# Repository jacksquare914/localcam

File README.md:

# LocalCam-1 — a local-only WiFi camera

A small 4-layer board that turns a **Luckfox Core1106** system-on-module (Rockchip
RV1106G3) into a network camera that never talks to anyone's cloud. A MIPI CSI-2 sensor
comes in over an FPC, the module encodes H.264/H.265 on-chip, and the stream is served
over RTSP to a local [Frigate](https://frigate.video/) NVR. Object detection runs on the
module's own 1 TOPS NPU, on the camera, not on a server and not on someone else's GPU.

**75 × 44 mm, 4 layers, 1.6 mm, built by JLCPCB.** USB-C in, microSD for storage, a
debug UART header and a recovery button.

> **Status: not ready to order.** 226 of 228 netted pads are connected. Two signals still
> need a trace and both need a part nudged rather than more routing effort — see
> [What is still open](#what-is-still-open). Everything else has been verified; the
> evidence is in [`logs/`](logs/).

---

## Why this board exists

Every consumer camera in this class wants an account, an app, and an outbound
connection. The goal here is the opposite: a camera that is useful precisely because it
is isolated. Four requirements drove the whole design.

1. **Nothing leaves the LAN.** No cloud service, no phone-home, no vendor account. RTSP
   to a local NVR and that is all.
2. **Detection happens on the camera.** The RV1106G3's NPU runs the model, so there is
   no video streaming off-box just so a server can look at it.
3. **It must be repairable and legible.** A board you cannot read is a board you cannot
   fix. That drove the routing style (below) as much as any electrical requirement.
4. **One cable.** USB-C supplies it; everything else is optional.

## What is on it

| | |
|---|---|
| **U1** | Luckfox Core1106 — RV1106G3, Cortex-A7 + RISC-V MCU + NPU + ISP, 256 MB DDR3L, onboard WiFi and 8 GB eMMC options |
| **J3** | 24-pin 0.5 mm FPC to the camera sensor — 2 MIPI data lanes + clock, I²C, MCLK, reset, power-down |
| **J1** | USB-C 2.0 receptacle — power in and USB device, with CC pull-downs and an ESD part (U2) |
| **J2** | microSD (Hirose DM3AT), 4-bit SDMMC, with card-detect |
| **H1** | 5-pin debug header — UART2 plus the recovery line |
| **S1** | reset, **D2** status LED, **F1** 1.5 A polyfuse, **D1** TVS on the 5 V rail |

Full pad-by-pad detail, cross-checked against the vendor pinout, is in
[`docs/pin-assignment-crosscheck.md`](docs/pin-assignment-crosscheck.md).

---

## The design decisions worth arguing about

[`docs/INTENT.md`](docs/INTENT.md) is the long version. The short version:

**The stack-up decides everything.** JLCPCB **JLC04161H-7628**: the 0.2104 mm of 7628
prepreg between F.Cu and the ground plane is the only reason the camera pairs can be
100 Ω. *If you let the fab substitute a stack-up, the pairs silently stop being 100 Ω.*
The order settings are printed by `hardware/make-fab.sh` for exactly that reason.

**In1.Cu is a plane, not a routing layer.** A MIPI pair's return current flows in the
copper directly beneath it; a slot cut in that plane is the classic reason a camera link
passes on the bench and drops frames when the enclosure warms up. The router physically
cannot place a non-GND track there.

**The camera pairs are routed as one trace, then split.** A single centreline is routed
at the full pair width and both traces are generated as parallel offsets of it, so the
gap is constant by construction and the lengths are identical:

| pair | leg / leg | intra-pair skew |
|---|---|---|
| CSI_D1 | 14.51 / 14.51 mm | **0 µm** |
| CSI_CLK | 14.72 / 14.72 mm | **0 µm** |
| CSI_D0 | 14.92 / 14.92 mm | **0 µm** |

Budget was 100 µm. Inter-pair spread is 410 µm against a 1000 µm budget. No pair changes
layer and no pair has a via.

**Orthogonal everywhere, with one deliberate exception.** Every trace runs parallel or
perpendicular to a board edge — 480-odd segments of it — except **18 chamfers, all six
of which belong to camera-pair traces**. Routed fully orthogonal the clock pair could not
stay coupled in the shared FPC channel and came out at 3.0 mm skew, which is a dead MIPI
link. Eighteen chamfers in one corridor buy back 0 µm on all three pairs. Everywhere
else there is room, so nothing cuts a corner.

**The USB-C data pads cross with no vias at all.** A 12-pin receptacle interleaves its
two D− pads with its two D+ pads at 0.5 mm pitch, so the two shorting links must cross
exactly once. A via pair does not fit — a 0.6 mm via needs 0.5 mm of clear radius and the
neighbouring pad edge is 0.35 mm away. So one net crosses *above* the pad row, inside the
connector body, and the other crosses *below* it. They never meet.

**Power rails live on In2.Cu, one via per group.** 0.5 mm of 1 oz outer copper carries
1.44 A at a 10 °C rise (IPC-2221) and the module draws about 0.6 A. +5V and VBUS_IN vias
are doubled, because a single plated barrel carrying a whole rail is the classic
warm-attic failure.

---

## Defects found and fixed along the way

These were real, and most were caught by review rather than by the person who made them.

| # | Defect | Why it mattered |
|---|---|---|
| A-7 | Pad 76 (`VCC3V3_RTC`) had been tied to +3V3 | It sits behind a Schottky inside the module; tying it shorts across that diode. Now deliberately unconnected. |
| A-8 | Camera I²C pull-ups went to +3V3 | Pads 16/17 are in the module's **1.8 V** IO domain — the vendor pinout confirms it. Pulling them to 3.3 V over-drives 1.8 V pins. Now on `+1V8`. |
| A-9 | `VBUS_DET` divider was fed from +3V3 | 100k/100k from 3.3 V gives 1.65 V into pad 24 (`USB_VBUSDET`, a **3.3 V** input) — *below* V_IH, so the pin sat in the indeterminate band. Now from +5V: 2.5 V, a valid high. |
| A-10/11 | No decoupling on +1V8; +5V bulk 71 mm from the module | ~60 mV of droop at 0.6 A with nothing local to absorb a WiFi transmit burst. Added C7 (100 nF on +1V8) and C8 (10 µF local +5V bulk). |
| A-12 | Ground pour ran flush to the board edge | Ignored the 2 mm corner fillets. Now inset 0.25 mm, following the radius. |
| A-13 | Three vias sat **inside pads** | Via-in-pad wicks solder paste during reflow and is not offered at this price tier. |
| A-14 | Two pairs of drills physically overlapped | −0.008 and −0.120 mm hole-to-hole against a 0.20 mm minimum. The fab would have rejected it. |
| A-15 | U2 (the USB ESD part) **was not grounded** | Its ground pad is fenced in by the USB traces, so the pour could not reach it. It now has its own via to the plane. |
| A-16 | The microSD **card-detect pins were not in the netlist at all** | J2 pins 9/10 had no net, so no connectivity check could report them. The stock `Micro_SD_Card` symbol has no such pins; J2 now uses `Micro_SD_Card_Det2`, which matches the DM3AT footprint pin for pin. |

A-15 and A-16 are the instructive ones: both were invisible to a net-level check. A net
with two pads and one trace looks complete whether or not a *third* pad is stranded, and
a pad with no net cannot be reported as disconnected at all. That is what
`tools/padaudit.py` exists to catch.

---

## Repo layout

```
hardware/     the KiCad 10 project — open LocalCam1.kicad_pro
  lib/        the Core1106 symbol and footprint (not in KiCad's stock libraries)
  make-fab.sh one-shot JLCPCB output generator; run it on a machine with KiCad 10
tools/        the sources of truth and the checkers
  spec.py       NETLIST source of truth — 36 parts, 36 nets. Edit this, never the schematic
  placement.py  PLACEMENT source of truth — part positions and the zone list
  gen.py        spec.py  -> LocalCam1.kicad_sch
  genpcb.py     spec.py + placement.py -> LocalCam1.kicad_pcb (placed, netted, unrouted)
  hroute5.py    the router (orthogonal, with coupled differential pairs)
  hroute6.py    the finisher — routes only what is missing, keeping existing copper
  continuity.py per-net island count + true minimum copper-to-copper gap
  padaudit.py   PER-PAD audit with the ground pour simulated  <- the one that finds real bugs
docs/         design intent, the pinout, the cross-check, routing and mechanical notes
vendor/       Luckfox's own Core1106 pinout spreadsheet, module PDF and footprint package
logs/         verification output, kept as evidence rather than summarised
```

## Building and checking it

The schematic and the board are **build outputs**. Do not hand-edit them and expect the
edit to survive.

```bash
cd tools
export KICAD_SYMBOL_DIR=/usr/share/kicad/symbols     # wherever yours live
python3 gen.py        # -> LocalCam1.kicad_sch
python3 genpcb.py     # -> LocalCam1.kicad_pcb  (placed, netted, unrouted)
python3 hroute5.py base.kicad_pcb routed.kicad_pcb   # route it
```

Then check it with something that did not do the routing:

```bash
python3 padaudit.py   ../hardware/LocalCam1.kicad_pcb   # per-pad, pour simulated
python3 continuity.py ../hardware/LocalCam1.kicad_pcb --clearance
```

`padaudit.py` walks every pad that carries a net and answers one question: is this pad in
the same electrical island as the rest of its net? It simulates the ground pour, because
the board ships with pours unfilled so KiCad recomputes them — without that simulation
every GND pad looks disconnected and the answer is useless.

**Fill the zones in KiCad (press `B`) and save before plotting**, or the pours are not in
the Gerbers and the ground plane simply does not exist.

Requires `numpy` and `scipy`.

## Verified, on the delivered board

```
226 / 228 netted pads connected        (pour simulated)
499 segments: 481 orthogonal, 18 chamfers on camera pairs, 0 other angles
108 vias, all 0.6 / 0.3 mm             (0.15 mm annular ring, min is 0.13)
minimum copper-to-copper gap 0.150 mm  (JLCPCB floor is 0.09)
camera pairs: 0 µm intra-pair skew, 410 µm inter-pair spread
45 of 45 used module pads agree with the vendor pinout
```

## What is still open

Two signals, both placement problems rather than routing ones:

| Net | Pad | At | What to do |
|---|---|---|---|
| `SD_D3` | J2.2 | (55.78, 28.51) | Six SD signals funnel through one gap between the module and the socket and D3 does not fit. Give it B.Cu with a via each side, or shift J2 about a millimetre. |
| `VBUS_DET` | R7.2 | (19.41, 32.60) | R7 sits in the channel the USB pair needs between U2 and the module edge. Move it clear — toward y ≈ 35.5 — or rotate it 90°. |

The router was given every chance at these: shape search, two-layer maze, two rip-up
rounds at widening corridors, and a last-resort pass at 0.15 mm / 0.10 mm. Each attempt
either gained nothing or broke three other nets to fix one, and reported that rather than
claiming a win.

**Open question for review:** `R7` currently divides **+5V** (post-fuse). Dividing
**VBUS_IN** (pre-fuse) is what the pin name literally means and still reads high if the
polyfuse opens; +5V instead answers "is my rail actually up?". Both give 2.5 V and both
are valid. One line in `spec.py`.

## Reviewing this board — where to look first

If you have ten minutes: [`docs/INTENT.md`](docs/INTENT.md) §4 for the arguable decisions,
then `logs/VERIFY-pads.log` for what is actually connected. If you have an hour, run
`padaudit.py` yourself and disagree with it.

Things I would most like a second opinion on:

- The two open nets above — is nudging R7 and J2 the right call, or should the floorplan
  change more deeply?
- The USB pair is **not** coupled between U1 and U2, because U2's +5V pin sits physically
  between D− and D+. Over ~8 mm at USB 2.0 that should be fine. Second opinion welcome.
- `+5V` reaches the module through a ~71 mm path. C8 was added locally to cover it, but a
  different floorplan would shorten the path instead.
- Whether grounding both card-detect pins is the right choice versus bringing one out to
  a GPIO with a pull-up.

## Sources

- Luckfox Core1106 pinout, schematic and footprint package —
  <https://wiki.luckfox.com/Core1106/Pinout/> (the files are mirrored in `vendor/`)
- Rockchip RV1106 datasheet V1.7 —
  <https://files.luckfox.com/wiki/Luckfox-Pico/PDF/Rockchip%20RV1106%20Datasheet%20V1.7-20231218.pdf>
- Core1106 product page — <https://www.luckfox.com/Core1106>
- Trace current capacity: IPC-2221. Differential microstrip geometry: IPC-2141.
- JLCPCB capabilities and the JLC04161H-7628 stack-up: JLCPCB's own capability pages.

## Licence

No licence has been chosen yet — which by default means all rights reserved, so pick one
before sharing this widely.

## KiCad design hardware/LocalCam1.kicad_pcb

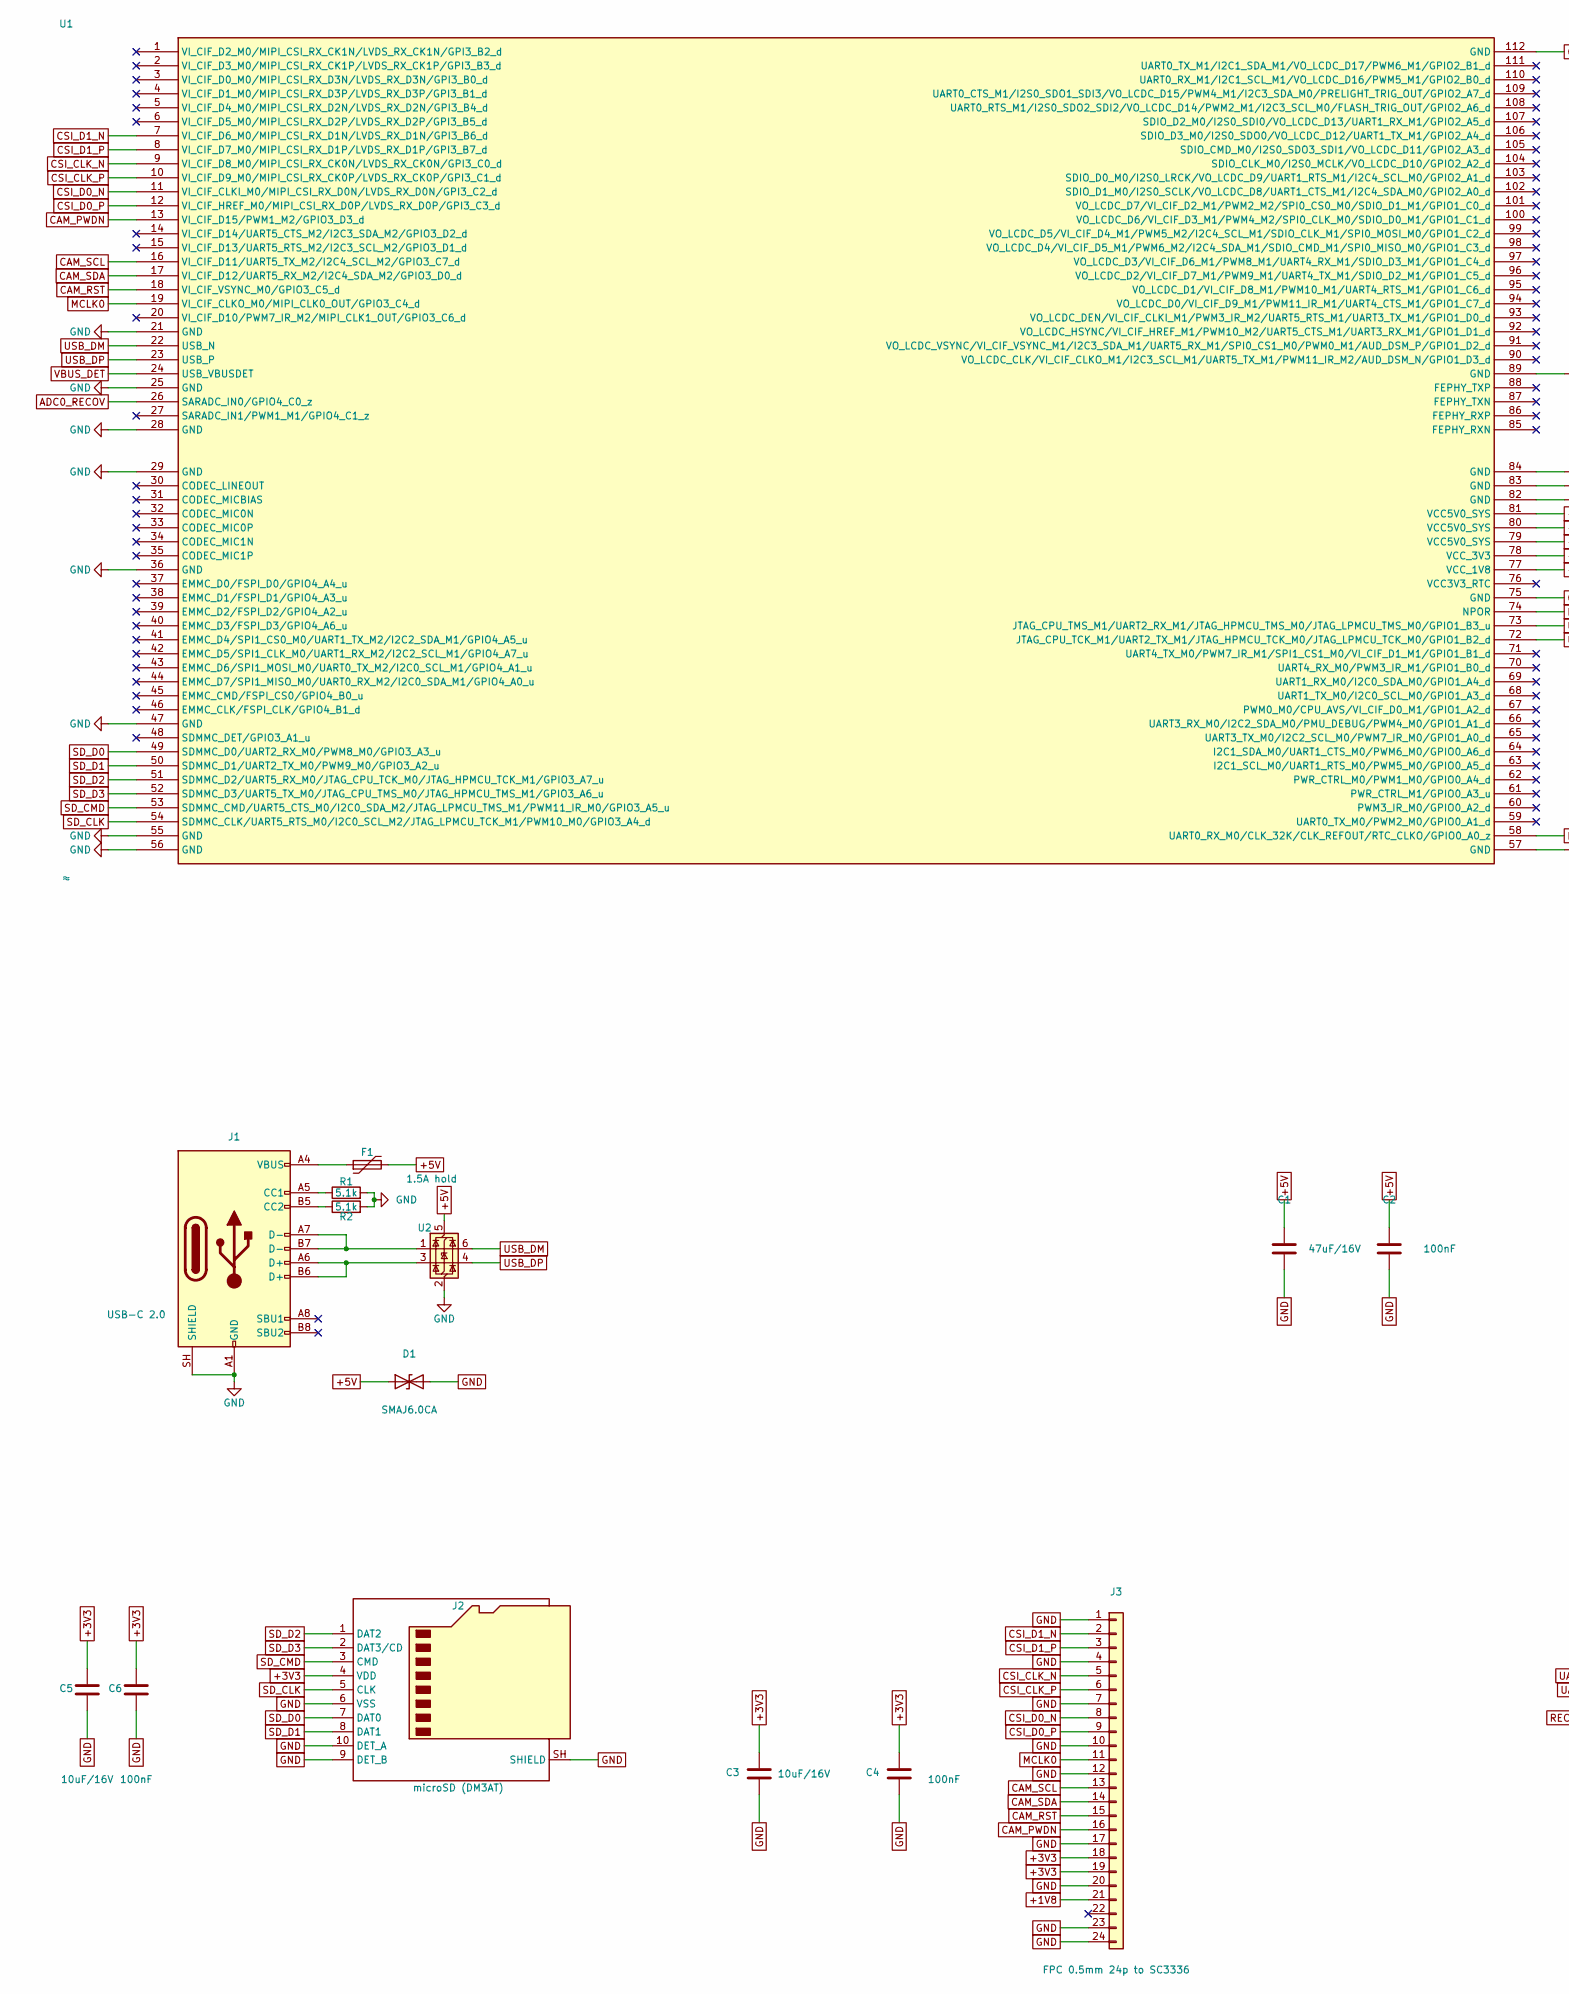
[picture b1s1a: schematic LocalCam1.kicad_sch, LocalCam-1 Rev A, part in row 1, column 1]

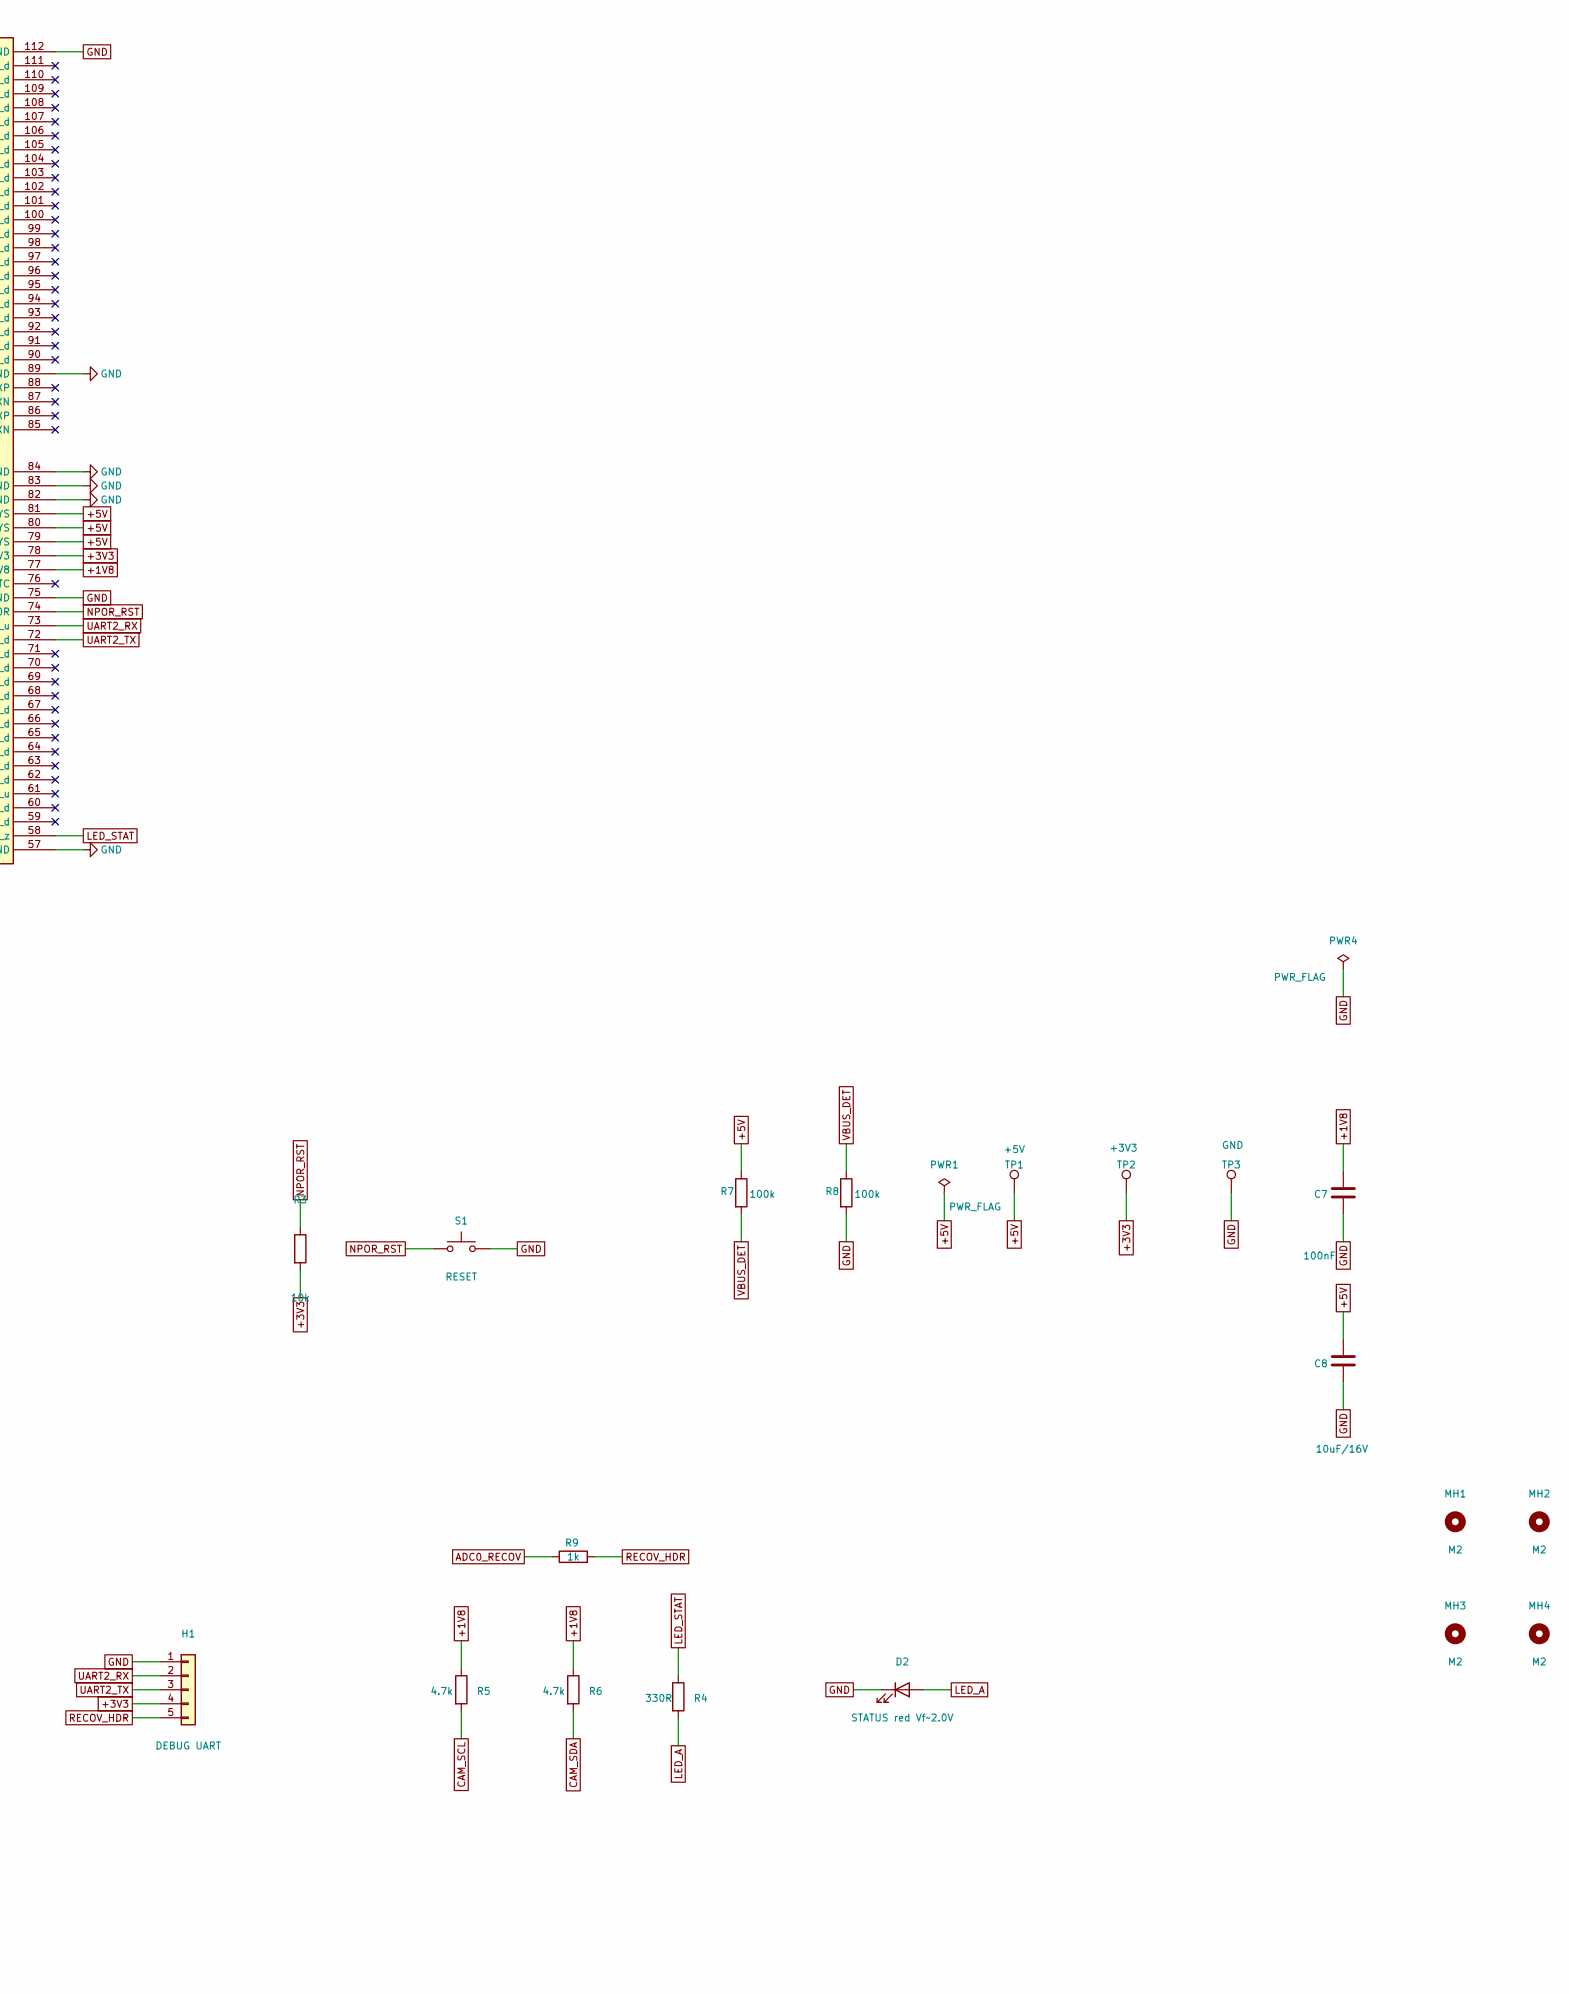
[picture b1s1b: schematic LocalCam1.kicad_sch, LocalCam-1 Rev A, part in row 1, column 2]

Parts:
C1: 47uF/16V; C_0805_2012Metric
C2, C4, C6, C7: 100nF; C_0402_1005Metric
C3, C5, C8: 10uF/16V; C_0805_2012Metric
D1: SMAJ6.0CA; D_SMA
D2: STATUS red Vf~2.0V; LED_0603_1608Metric
F1: 1.5A hold; R_1206_3216Metric
H1: DEBUG UART; PinHeader_1x05_P2.54mm_Vertical
J1: USB-C 2.0; USB_C_Receptacle_HRO_TYPE-C-31-M-12
J2: microSD (DM3AT); microSD_HC_Hirose_DM3AT-SF-PEJM5
J3: FPC 0.5mm 24p to SC3336; Hirose_FH12-24S-0.5SH_1x24-1MP_P0.50mm_Horizontal
MH1, MH2, MH3, MH4: M2; MountingHole_2.2mm_M2
PWR1, PWR4: PWR_FLAG
R1, R2: 5.1k; R_0402_1005Metric
R3: 10k; R_0402_1005Metric
R4: 330R; R_0402_1005Metric
R5, R6: 4.7k; R_0402_1005Metric
R7, R8: 100k; R_0402_1005Metric
R9: 1k; R_0402_1005Metric
S1: RESET; SW_Push_1P1T_NO_CK_KMR2
TP1: +5V; TestPoint_Pad_D1.5mm
TP2: +3V3; TestPoint_Pad_D1.5mm
TP3: GND; TestPoint_Pad_D1.5mm
U1: ≈; Core1106-SMT
U2: USBLC6-2SC6; SOT-23-6

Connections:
+1V8: C7.1, J3.21, R5.1, R6.1, U1.77 (VCC_1V8)
+3V3: C3.1, C4.1, C5.1, C6.1, H1.4, J2.4 (VDD), J3.18, J3.19, R3.2, TP2.1, U1.78 (VCC_3V3)
+5V: C1.1, C2.1, C8.1, D1.1 (A1), F1.2, PWR1.1, R7.1, TP1.1, U1.79 (VCC5V0_SYS), U1.80 (VCC5V0_SYS), U1.81 (VCC5V0_SYS), U2.5 (VBUS)
ADC0_RECOV: R9.1, U1.26 (SARADC_IN0/GPIO4_C0_z)
CAM_PWDN: J3.16, U1.13 (VI_CIF_D15/PWM1_M2/GPIO3_D3_d)
CAM_RST: J3.15, U1.18 (VI_CIF_VSYNC_M0/GPIO3_C5_d)
CAM_SCL: J3.13, R5.2, U1.16 (VI_CIF_D11/UART5_TX_M2/I2C4_SCL_M2/GPIO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)
CAM_SDA: J3.14, R6.2, U1.17 (VI_CIF_D12/UART5_RX_M2/I2C4_SDA_M2/GPIO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)
CC1: J1.A5 (CC1), R1.1
CC2: J1.B5 (CC2), R2.1
CSI_CLK_N: J3.5, U1.9 (VI_CIF_D8_M0/MIPI_CSI_RX_CK0N/LVDS_RX_C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)
CSI_CLK_P: J3.6, U1.10 (VI_CIF_D9_M0/MIPI_CSI_RX_CK0P/LVDS_RX_C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)
CSI_D0_N: J3.8, U1.11 (VI_CIF_CLKI_M0/MIPI_CSI_RX_D0N/LVDS_RX_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)
CSI_D0_P: J3.9, U1.12 (VI_CIF_HREF_M0/MIPI_CSI_RX_D0P/LVDS_RX_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)
CSI_D1_N: J3.2, U1.7 (VI_CIF_D6_M0/MIPI_CSI_RX_D1N/LVDS_RX_D1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)
CSI_D1_P: J3.3, U1.8 (VI_CIF_D7_M0/MIPI_CSI_RX_D1P/LVDS_RX_D1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)
GND: C1.2, C2.2, C3.2, C4.2, C5.2, C6.2, C7.2, C8.2, D1.2 (A2), D2.1 (K), H1.1, J1.A1 (GND), J1.A12 (GND), J1.B1 (GND), J1.B12 (GND), J1.SH (SHIELD), J2.6 (VSS), J2.9 (DET_B), J2.10 (DET_A), J2.SH (SHIELD), J3.1, J3.4, J3.7, J3.10, J3.12, J3.17, J3.20, J3.23, J3.24, PWR4.1, R1.2, R2.2, R8.2, S1.2, TP3.1, U1.21 (GND), U1.25 (GND), U1.28 (GND), U1.29 (GND), U1.36 (GND), U1.47 (GND), U1.55 (GND), U1.56 (GND), U1.57 (GND), U1.75 (GND), U1.82 (GND), U1.83 (GND), U1.84 (GND), U1.89 (GND), U1.112 (GND), U2.2 (GND)
LED_A: D2.2 (A), R4.2
LED_STAT: R4.1, U1.58 (UART0_RX_M0/CLK_32K/CLK_REFOUT/RTC_CLKO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)
MCLK0: J3.11, U1.19 (VI_CIF_CLKO_M0/MIPI_CLK0_OUT/GPIO3_C4_d)
NPOR_RST: R3.1, S1.1, U1.74 (NPOR)
RECOV_HDR: H1.5, R9.2
SD_CLK: J2.5 (CLK), U1.54 (SDMMC_CLK/UART5_RTS_M0/I2C0_SCL_M2/JTAG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)
SD_CMD: J2.3 (CMD), U1.53 (SDMMC_CMD/UART5_CTS_M0/I2C0_SDA_M2/JTAG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)
SD_D0: J2.7 (DAT0), U1.49 (SDMMC_D0/UART2_RX_M0/PWM8_M0/GPIO3_A3_u)
SD_D1: J2.8 (DAT1), U1.50 (SDMMC_D1/UART2_TX_M0/PWM9_M0/GPIO3_A2_u)
SD_D2: J2.1 (DAT2), U1.51 (SDMMC_D2/UART5_RX_M0/JTAG_CPU_TCK_M0/JT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)
SD_D3: J2.2 (DAT3/CD), U1.52 (SDMMC_D3/UART5_TX_M0/JTAG_CPU_TMS_M0/JT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)
UART2_RX: H1.2, U1.73 (JTAG_CPU_TMS_M1/UART2_RX_M1/JTAG_HPMCU_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)
UART2_TX: H1.3, U1.72 (JTAG_CPU_TCK_M1/UART2_TX_M1/JTAG_HPMCU_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)
USB_DM: U1.22 (USB_N), U2.6 (I/O1)
USB_DM_CON: J1.A7 (D-), J1.B7 (D-), U2.1 (I/O1)
USB_DP: U1.23 (USB_P), U2.4 (I/O2)
USB_DP_CON: J1.A6 (D+), J1.B6 (D+), U2.3 (I/O2)
VBUS_DET: R7.2, R8.1, U1.24 (USB_VBUSDET)
VBUS_IN: F1.1, J1.A4 (VBUS), J1.A9 (VBUS), J1.B4 (VBUS), J1.B9 (VBUS)

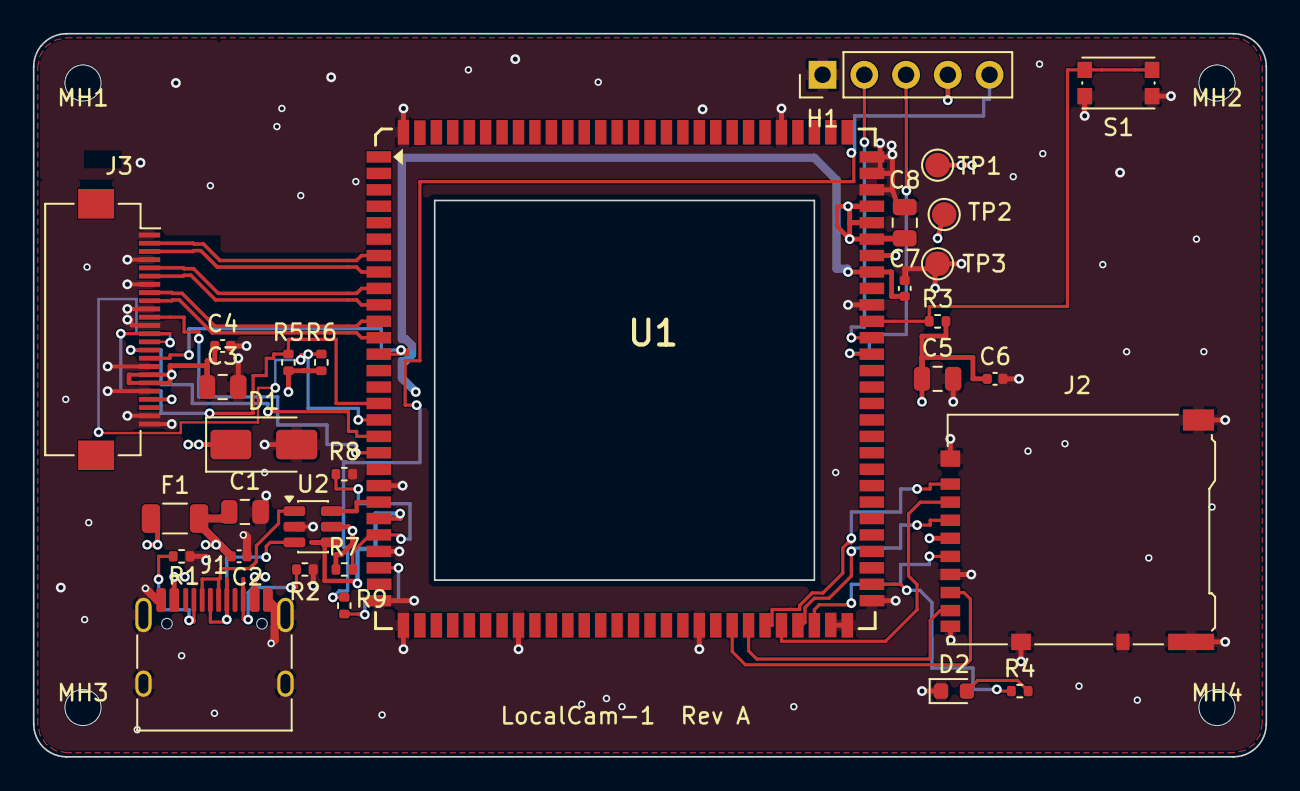
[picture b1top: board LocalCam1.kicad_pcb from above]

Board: 4 copper layers, 75.0 x 44.0 mm, 34 parts (0 on the bottom side), 36 nets.
